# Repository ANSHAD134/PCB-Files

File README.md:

# PCB-Files

A collection of my personal **KiCad PCB design projects**, custom symbol/footprint libraries, and 3D models used across different electronics builds.

---

## 📂 Repository Structure

```
PCB-Files/
├── 3D Models/                     # STEP files for 3D-printed / mechanical parts (motors, etc.)
├── KiCad Tools/
│   └── Symbol Libaries/           # Custom KiCad symbol libraries
├── Water Alarm/                   # Water level alarm PCB project (schematic + layout)
│   ├── Water Alarm.kicad_pro
│   ├── Water Alarm.kicad_sch
│   ├── Water Alarm.kicad_pcb
│   ├── FoodPrint Libraries/       # Custom footprints used in the project
│   ├── Graber/                    # Gerber export files
│   └── Water Alarm-backups/       # Auto-generated project backups
└── amplifier/                     # Audio amplifier PCB project
```

---

## 🔧 Projects

### 💧 Water Alarm
A KiCad project for a **water level detection alarm circuit** — includes schematic, PCB layout, custom footprints, and Gerber files ready for fabrication.

### 🔊 Amplifier
A KiCad-based **audio amplifier** PCB design.

### 🧩 3D Models
STEP (`.stp`) files for components (e.g. gear motors) used to preview real-world fit inside KiCad's 3D viewer.

### 📚 KiCad Tools / Symbol Libraries
Custom schematic symbol libraries reused across multiple projects for easier and consistent design work.

---

## 🛠️ Getting Started

1. Install **[KiCad](https://www.kicad.org/download/)** (v7 or later recommended).
2. Clone this repository:
   ```bash
   git clone https://github.com/ANSHAD134/PCB-Files.git
   ```
3. Open any project's `.kicad_pro` file in KiCad to view/edit the schematic and PCB layout.
4. Gerber files (inside `Graber/` folders) can be sent directly to a PCB fab (JLCPCB, PCBWay, etc.) for manufacturing.

---

## 📄 License

This project is open for personal and educational use. Feel free to fork and modify for your own builds. Add a `LICENSE` file (e.g. MIT) if you'd like to make the terms official.

---

## 🙋 Author

**ANSHAD134** — [GitHub Profile](https://github.com/ANSHAD134)

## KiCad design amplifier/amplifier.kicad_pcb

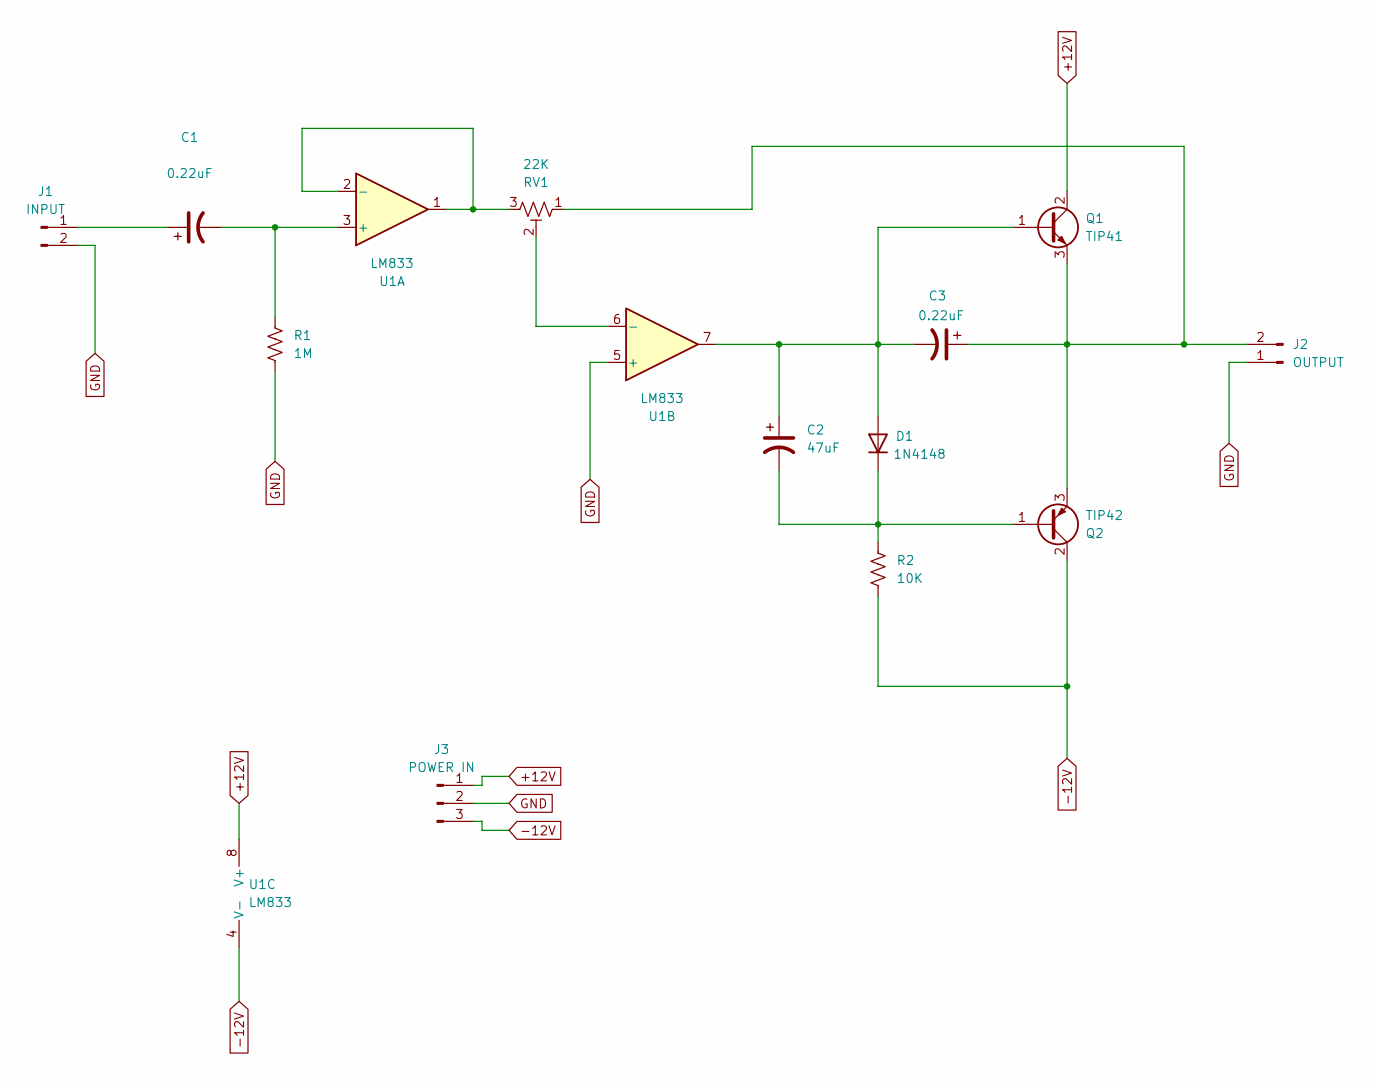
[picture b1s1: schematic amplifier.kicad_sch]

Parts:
C1, C3: 0.22uF; CP_Radial_D5.0mm_P2.50mm
C2: 47uF; CP_Radial_D5.0mm_P2.50mm
D1: 1N4148; D_DO-35_SOD27_P7.62mm_Horizontal
J1: INPUT; PinHeader_1x02_P2.54mm_Vertical
J2: OUTPUT; Altech_AK300_1x02_P5.00mm_45-Degree
J3: POWER IN; Altech_AK300_1x03_P5.00mm_45-Degree
Q1: TIP41; TO-220-3_Vertical
Q2: TIP42; TO-220-3_Vertical
R1: 1M; R_Axial_DIN0207_L6.3mm_D2.5mm_P10.16mm_Horizontal
R2: 10K; R_Axial_DIN0207_L6.3mm_D2.5mm_P10.16mm_Horizontal
RV1: 22K; Potentiometer_Piher_PT-15-V15_Vertical
U1: LM833; DIP-8_W7.62mm_LongPads

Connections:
+12V: J3.1, Q1.2 (C), U1.8 (V+)
-12V: J3.3, Q2.2 (C), R2.2, U1.4 (V-)
GND: J1.2, J2.1, J3.2, R1.2, U1.5 (+)
unnamed: C2.1, C3.2, D1.2 (A), Q1.1 (B), U1.7
unnamed: C2.2, D1.1 (K), Q2.1 (B), R2.1
unnamed: C1.1, J1.1
unnamed: C3.1, J2.2, Q1.3 (E), Q2.3 (E), RV1.1
unnamed: C1.2, R1.1, U1.3 (+)
unnamed: RV1.3, U1.1, U1.2 (-)
unnamed: RV1.2, U1.6 (-)

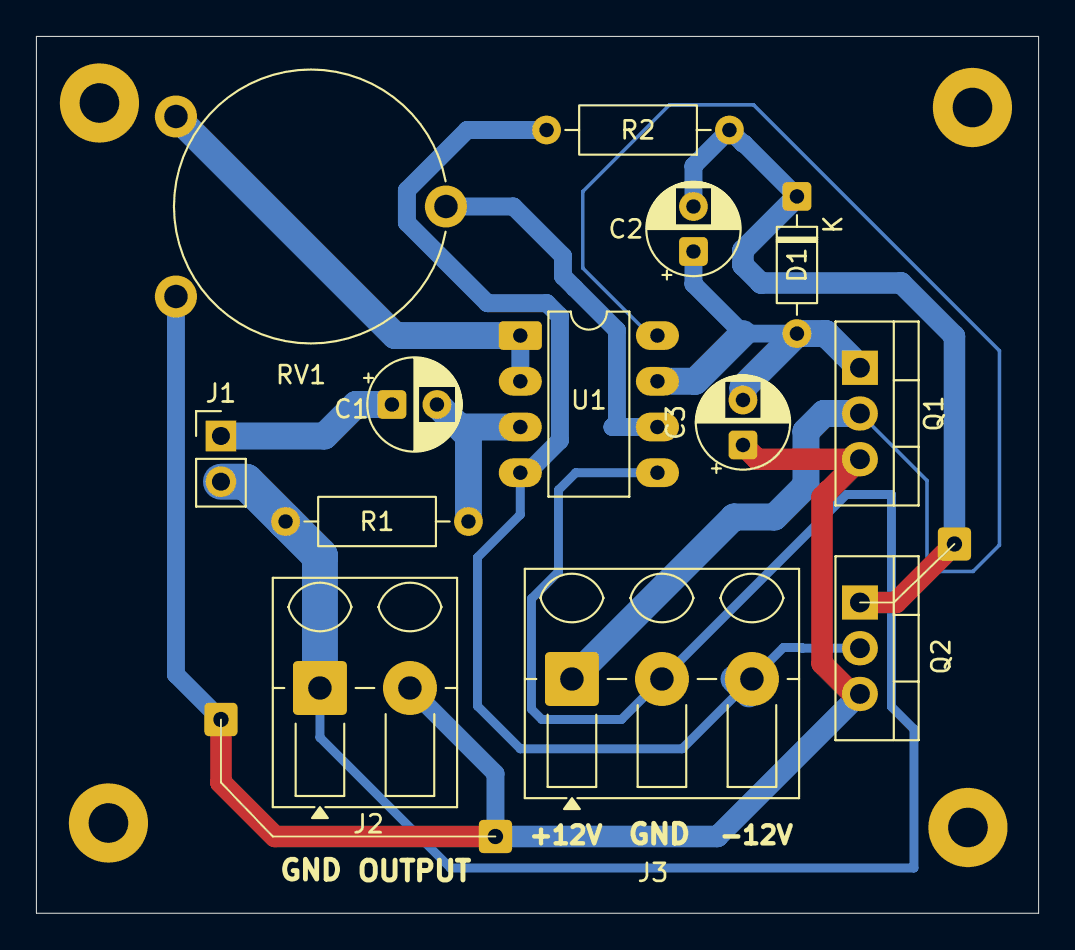
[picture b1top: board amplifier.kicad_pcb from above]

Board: 2 copper layers, 55.7 x 48.7 mm, 17 parts (0 on the bottom side), 10 nets.

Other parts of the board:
., .#2, .#3, .#4: MountingHole_2.2mm_M2_Pad

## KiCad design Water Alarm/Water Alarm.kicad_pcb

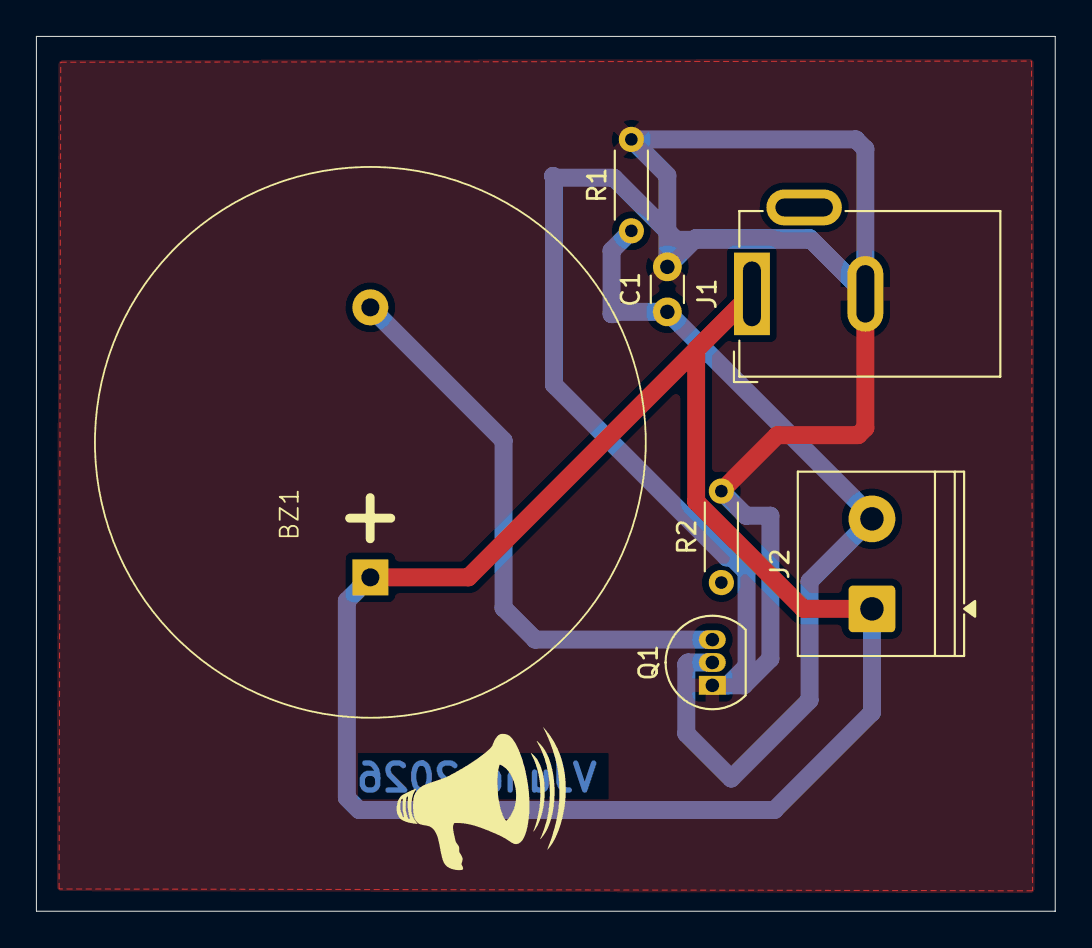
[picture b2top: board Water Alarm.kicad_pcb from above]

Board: 2 copper layers, 56.6 x 48.6 mm, 7 parts (0 on the bottom side), 4 nets.

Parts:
BZ1: Buzzer; Buzzer_D30mm_H20mm_P15mm__668-1652-ND__AI-3035-TT-12V-R
C1: 1nF; C_Disc_D3.0mm_W1.6mm_P2.50mm
J1: Jack-DC; BarrelJack_GCT_DCJ200-10-A_Horizontal
J2: Screw_Terminal_01x02; TerminalBlock_Phoenix_PT-1,5-2-5.0-H_1x02_P5.00mm_Horizontal
Q1: 2N7000; TO-92_Inline
R1: 10M; R_Axial_DIN0204_L3.6mm_D1.6mm_P5.08mm_Horizontal
R2: 6.8K; R_Axial_DIN0204_L3.6mm_D1.6mm_P5.08mm_Horizontal

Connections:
/Gate: C1.1, J2.2, Q1.2 (G), R1.1
GND: C1.2, J1.2, Q1.1 (S), R1.2, R2.2
unnamed: BZ1.2 (-), Q1.3 (D)
VCC: BZ1.1 (+), J1.1, J2.1

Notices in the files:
README.md:
License: MIT
